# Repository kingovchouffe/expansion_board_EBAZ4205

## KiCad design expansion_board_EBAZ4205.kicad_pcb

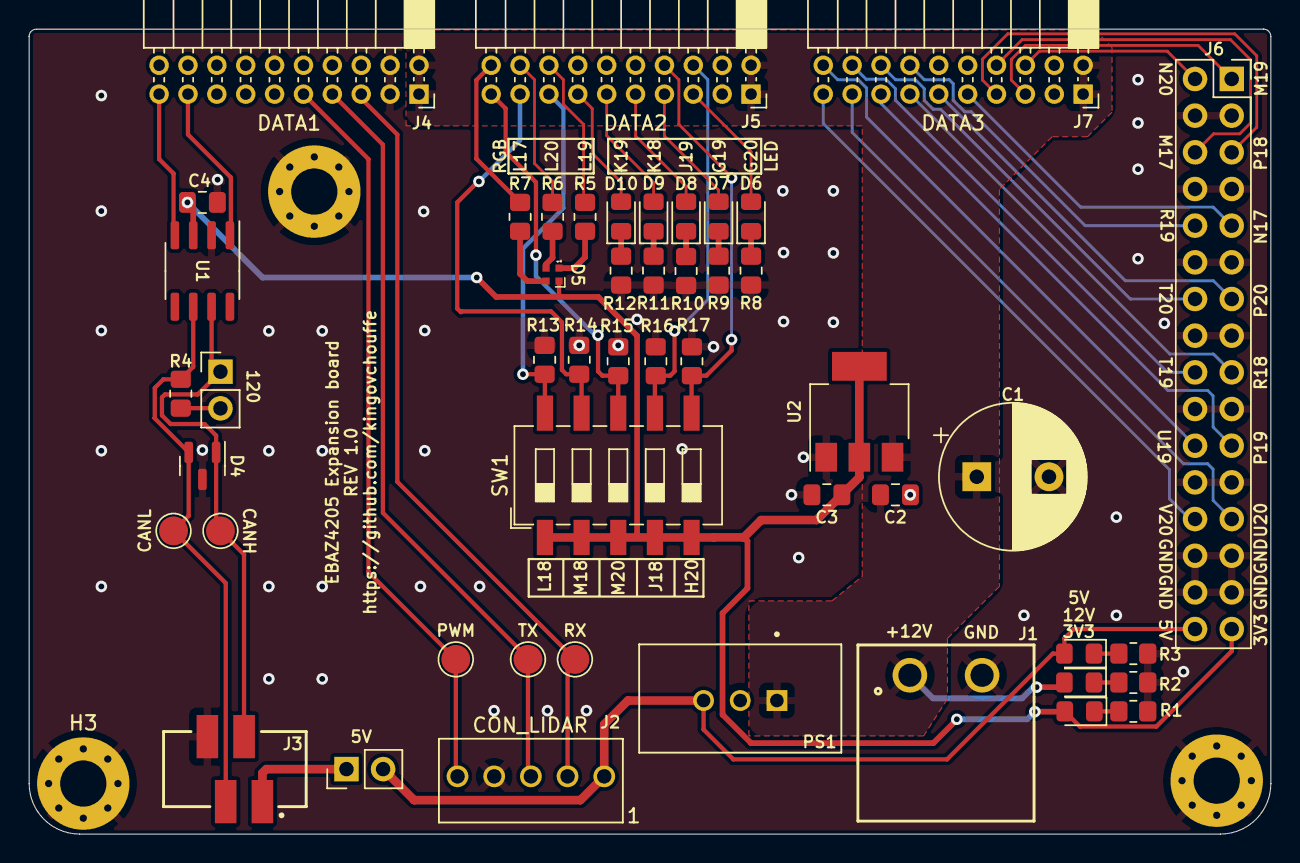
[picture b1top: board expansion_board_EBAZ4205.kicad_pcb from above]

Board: 2 copper layers, 86.0 x 55.8 mm, 52 parts (0 on the bottom side), 51 nets.

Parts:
3V3: 3V3; LED_0805_2012Metric_Pad1.15x1.40mm_HandSolder
5V: 5V; LED_0805_2012Metric_Pad1.15x1.40mm_HandSolder
5V#2: 5V; PinHeader_1x02_P2.54mm_Vertical
12V: 12V; LED_0805_2012Metric_Pad1.15x1.40mm_HandSolder
120: 120; PinHeader_1x02_P2.54mm_Vertical
C1: 100u; CP_Radial_D10.0mm_P5.00mm
C2, C3: 10u; C_0805_2012Metric_Pad1.18x1.45mm_HandSolder
C4: 100n; C_0805_2012Metric_Pad1.18x1.45mm_HandSolder
CANH: CANL; TestPoint_Pad_D2.0mm
CANL: CANL; TestPoint_Pad_D2.0mm
D4: D_TVS_x2_AAC; SOT-23
D5: LED_RGBA; LED_SK6812_EC15_1.5x1.5mm
D6: LED1; LED_0805_2012Metric_Pad1.15x1.40mm_HandSolder
D7: LED2; LED_0805_2012Metric_Pad1.15x1.40mm_HandSolder
D8, D9, D10: LED3; LED_0805_2012Metric_Pad1.15x1.40mm_HandSolder
H1, H3, H4: MountingHole_Pad; MountingHole_3.2mm_M3_Pad_Via
J1: INPUT; Wuerth_batcon_691313710002
J2: CON_LIDAR; Wuerth_2.54mm_5pins_61900511121
J3: CON_CAN; 690367290476
J4: DATA1; PinSocket_2x10_P2.00mm_Horizontal
J5: DATA2; PinSocket_2x10_P2.00mm_Horizontal
J6: DATA3_2.54; PinSocket_2x16_P2.54mm_Vertical
J7: DATA3; PinSocket_2x10_P2.00mm_Horizontal
PS1: TSR_2-2450; CONV_TSR_2-2450
PWM: PWM_MOT; TestPoint_Pad_D2.0mm
R1, R4, R5, R6, R7, R8, R9, R10, R11, R12: 120; R_0805_2012Metric_Pad1.20x1.40mm_HandSolder
R2: 560; R_0805_2012Metric_Pad1.20x1.40mm_HandSolder
R3: 280; R_0805_2012Metric_Pad1.20x1.40mm_HandSolder
R13, R14, R15, R16, R17: 10k; R_0805_2012Metric_Pad1.20x1.40mm_HandSolder
RX: RX; TestPoint_Pad_D2.0mm
SW1: SW_DIP_x05; SW_DIP_SPSTx05_Slide_6.7x14.26mm_W8.61mm_P2.54mm_LowProfile
TX: TX; TestPoint_Pad_D2.0mm
U1: SN65HVD232; SOIC-8_3.9x4.9mm_P1.27mm
U2: NCP1117-3.3_SOT223; SOT-223-3_TabPin2

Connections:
+3V3: 3V3.2 (A), C3.2, C4.1, D5.4 (A), J6.31, SW1.1, SW1.2, SW1.3, SW1.4, SW1.5, U1.3 (VCC), U2.2 (VO)
+5V: 5V.2 (A), 5V#2.2, J2.1, J6.32, PS1.3 (+VOUT)
+12V: 12V.2 (A), C1.1, C2.2, J1.1, J4.1, J4.2, J5.1, J5.2, J7.1, J7.2, PS1.1 (+VIN), U2.3 (VI)
/A20: J2.2, J4.5, RX.1
/B19: J2.3, J4.7, TX.1
/Bleu: D5.1 (RK), R5.1
/C20: J2.5, J4.9, PWM.1
/CANH: 120.1, CANH.1, D4.1 (A1), J3.2, U1.7 (CANH)
/CANL: CANL.1, D4.2 (A2), J3.3, R4.1, U1.6 (CANL)
/F19: J4.19, U1.4 (R)
/F20: J4.17, U1.1 (D)
/G19: D7.2 (A), J5.7
/G20: D6.2 (A), J5.5
/H20: J5.8, R17.2, SW1.6
/J18: J5.6, R16.2, SW1.7
/J19: D8.2 (A), J5.9
/K18: D9.2 (A), J5.11
/K19: D10.2 (A), J5.13
/L16: J5.15, R13.2, SW1.10
/L17: J5.20, R7.2
/L19: J5.16, R5.2
/L20: J5.18, R6.2
/M17: J6.6, J7.8
/M18: J5.17, R14.2, SW1.9
/M19: J6.1, J7.5
/M20: J5.19, R15.2, SW1.8
/N17: J6.9, J7.9
/N20: J6.2, J7.6
/P18: J6.5, J7.7
/P19: J6.21, J7.15
/P20: J6.13, J7.11
/R18: J6.17, J7.13
/R19: J6.10, J7.14
/Rouge: D5.3 (BK), R7.1
/T19: J6.18, J7.18
/T20: J6.14, J7.16
/U19: J6.22, J7.20
/U20: J6.25, J7.17
/V20: J6.26, J7.19
/Vert: D5.2 (GK), R6.1
GND: C1.2, C2.1, C3.1, C4.2, D4.3 (common), H1.1, H3.1, H4.1, J1.2, J2.4, J3.4, J4.3, J4.4, J4.12, J5.3, J5.4, J5.12, J6.3, J6.4, J6.7, J6.8, J6.11, J6.12, J6.15, J6.16, J6.19, J6.20, J6.23, J6.24, J6.27, J6.28, J6.29, J6.30, J7.3, J7.4, J7.12, PS1.2 (GND), R1.2, R2.2, R3.2, R8.2, R9.2, R10.2, R11.2, R12.2, R13.1, R14.1, R15.1, R16.1, R17.1, U1.2 (GND), U2.1 (GND)
unnamed: 3V3.1 (K), R1.1
unnamed: 12V.1 (K), R2.1
unnamed: 5V.1 (K), R3.1
unnamed: D6.1 (K), R8.1
unnamed: D7.1 (K), R9.1
unnamed: D8.1 (K), R10.1
unnamed: D9.1 (K), R11.1
unnamed: D10.1 (K), R12.1
unnamed: 5V#2.1, J3.1
unnamed: 120.2, R4.2

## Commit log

2022-09-27 update pdf
